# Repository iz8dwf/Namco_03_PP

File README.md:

# Namco_03_PP
Namco 03xx custom IC replacement for Pole Position video PCB

This daughterboard replaces the two 03XX custom ICs at 5L and 6L on
a Pole Position (or Pole Position II) Video PCB. It uses a single atf1504
CPLD to implement partially both 03XX ICs. Original 03XX are 6 bits wide, 
4 bits deep shift register with configurable depth. See the CPLD source file
for more information. Pole Position only uses 4 bits of the 6 bits and
the clock pin of both ICs is driven by the same signal, so that's
what I've implemented. A general purpose replacement with full 6 bits can 
in theory be implemented on a single atf1502 but I haven't tested it.

(Fun) Fact: one original 03XX IC has been reverse engineered with the help of
a Commodore PET 3032 machine using its 8 bit bi-directional user port and a few
Basic programs. These are "static" ICs so clock can be toggled even at a few seconds
intervals if needed.

THE JTAG PINOUT IS NOT STANDARD!

USE AT YOUR OWN RISK

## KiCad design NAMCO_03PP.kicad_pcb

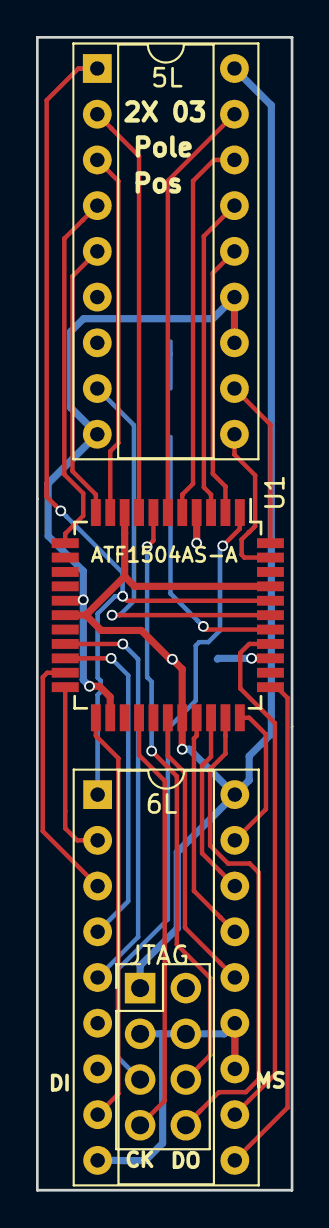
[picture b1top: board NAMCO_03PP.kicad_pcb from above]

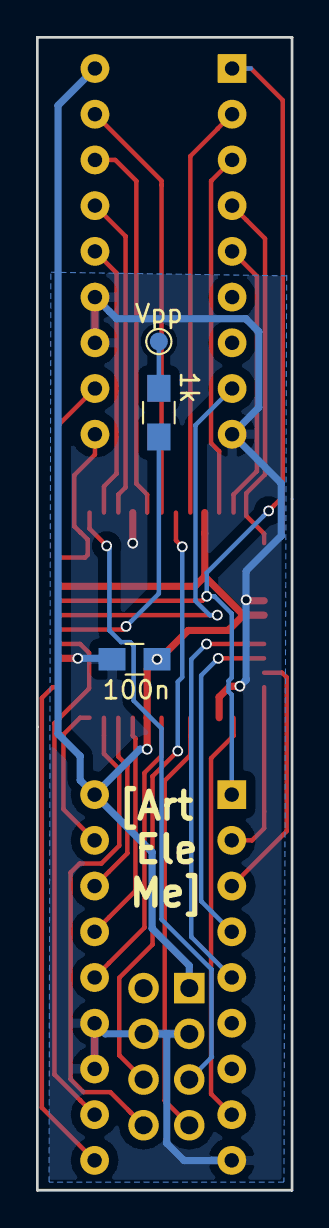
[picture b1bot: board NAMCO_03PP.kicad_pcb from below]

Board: 2 copper layers, 14.1 x 64.0 mm, 7 parts (3 on the bottom side), 31 nets.

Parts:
5L, 6L: DIP18; DIP-18_W7.62mm_Socket
C1: 100n; C_0805_HandSoldering
J1: JTAG; Pin_Header_Straight_2x04_Pitch2.54mm
J2: Vpp; Test_Point_Pad_d1.0mm
R1: 1k; R_0805_HandSoldering
U1: ATF1504AS-A; TQFP-44_10x10mm_Pitch0.8mm

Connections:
/I10: 5L.2, U1.8
/I11: 5L.3, U1.10
/I12: 5L.4, U1.12
/I13: 5L.5, U1.11
/I20: 6L.2, U1.22
/I21: 6L.3, U1.21
/I22: 6L.4, U1.20
/I23: 6L.5, U1.19
/O10: 5L.17, U1.6
/O11: 5L.16, U1.5
/O12: 5L.15, U1.3
/O13: 5L.14, U1.2
/O20: 6L.17, U1.33
/O21: 6L.16, U1.31
/O22: 6L.15, U1.30
/O23: 6L.14, U1.28
/OUT_SEL1: 5L.8, U1.39
/OUT_SEL2: 6L.8, U1.23
/QSL10: 5L.10, U1.43
/QSL11: 5L.11, U1.44
/QSL20: 6L.10, U1.34
/QSL21: 6L.11, U1.37
/~6M: 5L.1, 6L.1, U1.40
GND: 5L.9, 5L.12, 5L.13, 6L.9, 6L.12, 6L.13, C1.2, J1.3, J1.4, U1.4, U1.16, U1.24, U1.36
unnamed: J1.5, U1.1
unnamed: J1.6, U1.7
unnamed: J1.7, U1.26
unnamed: J1.8, U1.32
unnamed: J2.1, R1.1
unnamed: R1.2, U1.38
VCC: 5L.18, 6L.18, C1.1, J1.1, U1.9, U1.17, U1.29, U1.41

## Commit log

2024-08-16 Initial release
2024-08-16 Added picture
2024-08-16 Better implementation details
2024-09-02 file mode change
2024-09-13 cpld field corrected
